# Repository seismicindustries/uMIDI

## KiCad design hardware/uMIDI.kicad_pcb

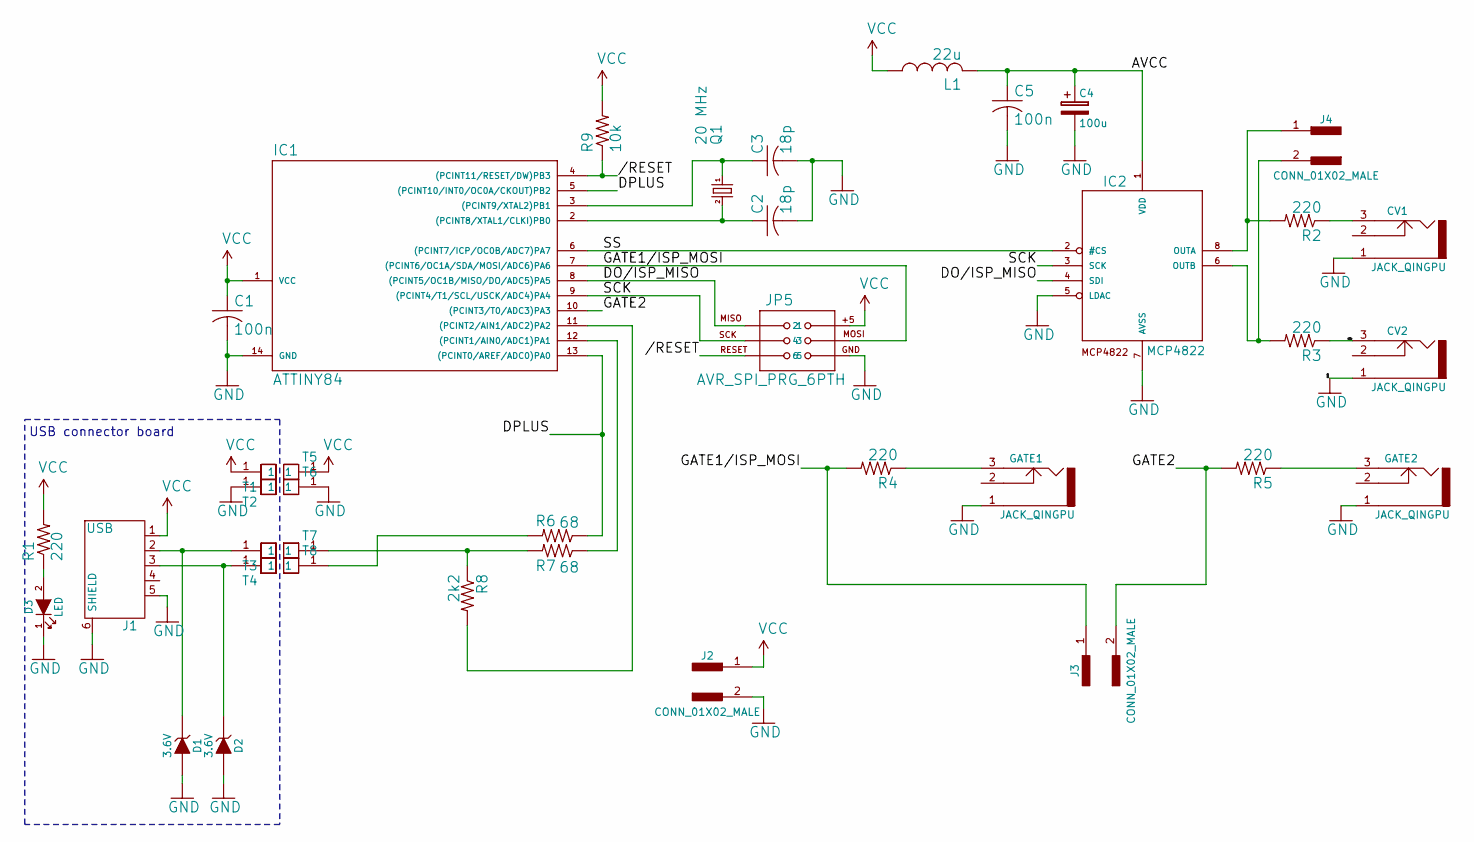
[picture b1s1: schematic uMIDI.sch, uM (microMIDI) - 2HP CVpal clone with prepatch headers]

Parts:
C1, C5: 100n; C_0603; MPN C0603C104Z3VACTU
C2, C3: 18p; C_0603; MPN VJ0603A180JXACW1BC
C4: 100u; C_Radial_D4_L7; MPN ECE-A0JKA101
CV1, CV2: JACK_QINGPU; jack_qingpu
D1, D2: 3.6V; SOD-323; MPN BZX384B3V6-E3-18
D3: LED; LED_D3.0mm; MPN LTL-4231N
GATE1, GATE2: JACK_QINGPU; jack_qingpu
IC1: ATTINY84; SOIC-14_N; MPN ATTINY84A-SSU
IC2: MCP4822; SO-8; MPN MCP4822-E/SN
J1: USB; ZX62D-B-MICRO_USB_RECEIPTABLE; MPN ZX62D-B-5PA8(30)
J2, J3, J4: CONN_01X02_MALE; Pin_Header_Angled_2x01_Pitch2.54mm
JP5: AVR_SPI_PRG_6PTH; Pin_Header_Straight_2x03_Pitch2.54mm; MPN 103777-3
L1: 22u; Inductor_SRN4018TA_bourns; MPN SRN4018TA-220M
Q1: 20 MHz; ABM7; MPN ABM7-20.000MHZ-D2Y-T
R1, R2, R3, R4, R5: 220; R_0603; MPN CRCW0603220RFKEB
R6, R7: 68; R_0603; MPN Panasonic
R8: 2k2; R_0603; MPN RC0603FR-072K2L
R9: 10k; R_0603; MPN RC0603FR-0710KL
T1, T2, T3, T4, T5, T6, T7, T8: TESTPIN; TESTPAD_SMD_SQR

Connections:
//RESET: IC1.4 ((PCINT11/RESET/DW)PB3), JP5.5, R9.1
/AVCC: C4.1, C5.1, IC2.1 (VDD), L1.2
/DO/ISP_MISO: IC1.8 ((PCINT5/OC1B/MISO/DO/ADC5)PA5), IC2.4 (SDI), JP5.1
/DPLUS: IC1.5 ((PCINT10/INT0/OC0A/CKOUT)PB2), IC1.13 ((PCINT0/AREF/ADC0)PA0), R6.1
/GATE1/ISP_MOSI: IC1.7 ((PCINT6/OC1A/SDA/MOSI/ADC6)PA6), J3.1, JP5.4, R4.2
/GATE2: IC1.10 ((PCINT3/T0/ADC3)PA3), J3.2, R5.2
/N$4: CV2.3, R3.1
/SCK: IC1.9 ((PCINT4/T1/SCL/USCK/ADC4)PA4), IC2.3 (SCK), JP5.3
/SS: IC1.6 ((PCINT7/ICP/OC0B/ADC7)PA7), IC2.2 (#CS)
GND: C1.2, C2.2, C3.2, C4.2, C5.2, CV1.1, CV2.1, D1.2 (A), D2.2 (A), D3.1 (K), GATE1.1, GATE2.1, IC1.14 (GND), IC2.5 (LDAC), IC2.7 (AVSS), J1.5, J1.6 (SHIELD), J2.2, JP5.6, T2.1, T6.1
unnamed: C2.1, IC1.2 ((PCINT8/XTAL1/CLKI)PB0), Q1.2
unnamed: C3.1, IC1.3 ((PCINT9/XTAL2)PB1), Q1.1
unnamed: CV1.3, R2.1
unnamed: D1.1 (K), J1.2, T3.1
unnamed: D2.1 (K), J1.3, T4.1
unnamed: D3.2 (A), R1.1
unnamed: GATE1.3, R4.1
unnamed: GATE2.3, R5.1
unnamed: IC1.11 ((PCINT2/AIN1/ADC2)PA2), R8.2
unnamed: IC1.12 ((PCINT1/AIN0/ADC1)PA1), R7.1
unnamed: IC2.6 (OUTB), J4.2, R3.2
unnamed: IC2.8 (OUTA), J4.1, R2.2
unnamed: R6.2, T8.1
unnamed: R7.2, R8.1, T7.1
VCC: C1.1, IC1.1 (VCC), J1.1, J2.1, JP5.2, L1.1, R1.2, R9.2, T1.1, T5.1

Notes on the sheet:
USB connector board

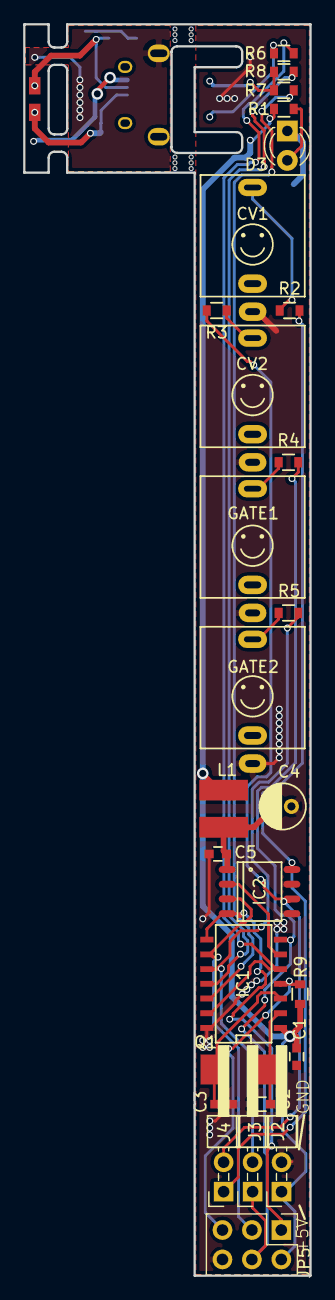
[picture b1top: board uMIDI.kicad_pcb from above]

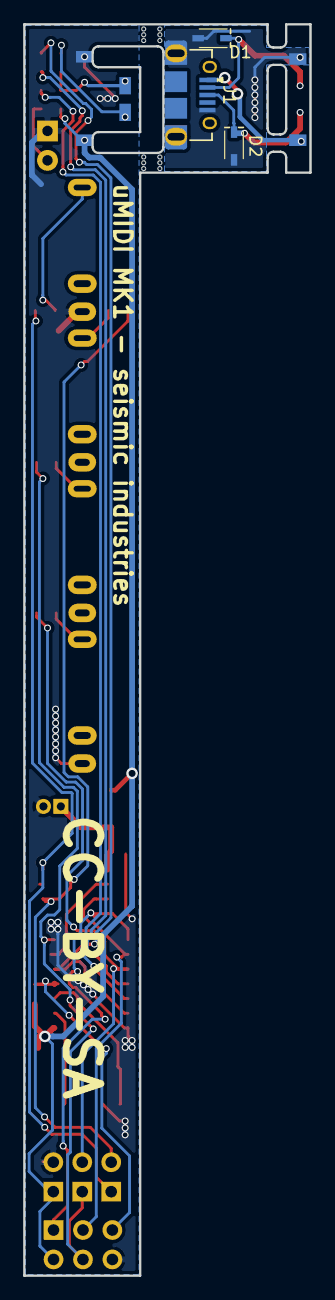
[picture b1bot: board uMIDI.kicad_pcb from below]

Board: 2 copper layers, 24.7 x 108.0 mm, 38 parts (9 on the bottom side), 25 nets.

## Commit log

2018-05-31 clean gerber folder
2018-06-01 license info added

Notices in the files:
hardware/uMIDI.kicad_pcb:
CC-BY-SA
hardware/uMIDI.sch:
License: CC-BY-SA 3.0
